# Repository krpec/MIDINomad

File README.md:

# MIDI Nomad

Arduino-based MIDI capable footswitch replacement for Mesa/Boogie Nomad 100 head.

Inspired by [happyswitch](https://happyswitch.it), [happyswitch github repo](https://github.com/siddolo/happyswitch)

Hackaday.io project can be found here: [MIDI Nomad](https://hackaday.io/project/170576-midi-nomad)

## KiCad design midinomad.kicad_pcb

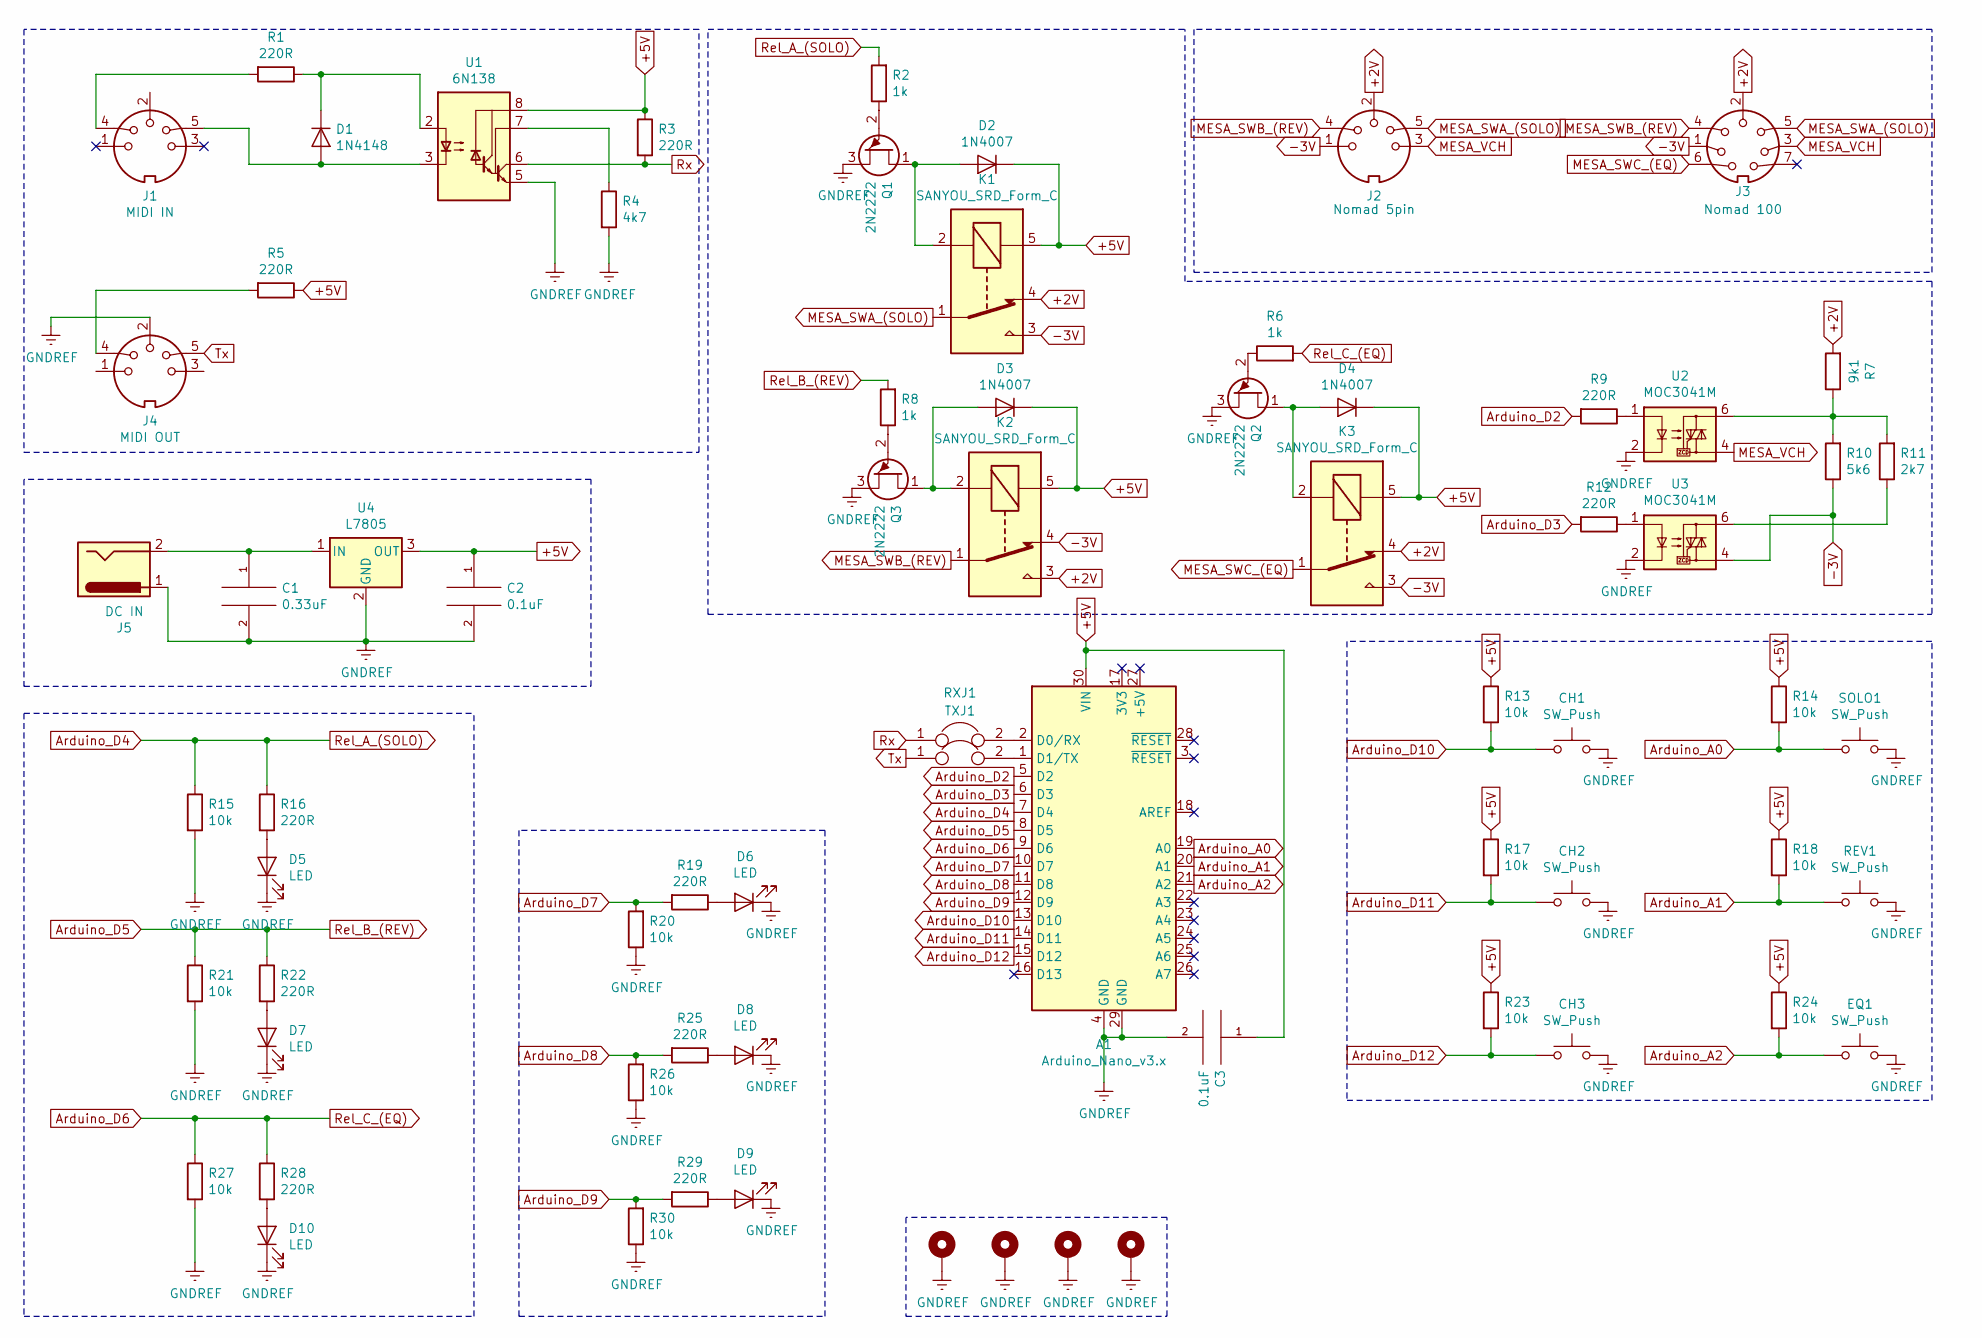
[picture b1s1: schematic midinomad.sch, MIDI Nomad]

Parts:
A1: Arduino_Nano_v3.x; Arduino_Nano
C1: 0.33uF; C_Disc_D6.0mm_W2.5mm_P5.00mm
C2, C3: 0.1uF; C_Disc_D6.0mm_W2.5mm_P5.00mm
CH1, CH2, CH3: SW_Push; SW_PUSH_6mm
D1: 1N4148; D_DO-35_SOD27_P7.62mm_Horizontal
D2, D3, D4: 1N4007; D_DO-41_SOD81_P10.16mm_Horizontal
D5, D6, D7, D8, D9, D10: LED; LED_D5.0mm
EQ1: SW_Push; SW_PUSH_6mm
H1, H2, H3, H4: MountingHole_Pad; MountingHole_3.2mm_M3_DIN965_Pad
J1: MIDI IN; din-5
J2: Nomad 5pin; din-5
J3: Nomad 100; din-8
J4: MIDI OUT; din-5
J5: DC IN; BarrelJack_Horizontal
K1, K2, K3: SANYOU_SRD_Form_C; Relay_SPDT_SANYOU_SRD_Series_Form_C
Q1, Q2, Q3: 2N2222; TO-92
R1, R3, R5, R9, R12, R16, R19, R22, R25, R28, R29: 220R; R_Axial_DIN0207_L6.3mm_D2.5mm_P10.16mm_Horizontal
R2, R6, R8: 1k; R_Axial_DIN0207_L6.3mm_D2.5mm_P10.16mm_Horizontal
R4: 4k7; R_Axial_DIN0207_L6.3mm_D2.5mm_P10.16mm_Horizontal
R7: 9k1; R_Axial_DIN0207_L6.3mm_D2.5mm_P10.16mm_Horizontal
R10: 5k6; R_Axial_DIN0207_L6.3mm_D2.5mm_P10.16mm_Horizontal
R11: 2k7; R_Axial_DIN0207_L6.3mm_D2.5mm_P10.16mm_Horizontal
R13, R14, R15, R17, R18, R20, R21, R23, R24, R26, R27, R30: 10k; R_Axial_DIN0207_L6.3mm_D2.5mm_P10.16mm_Horizontal
REV1: SW_Push; SW_PUSH_6mm
RXJ1: Jumper; PinHeader_1x02_P2.54mm_Vertical
SOLO1: SW_Push; SW_PUSH_6mm
TXJ1: Jumper; PinHeader_1x02_P2.54mm_Vertical
U1: 6N138; DIP-8_W7.62mm
U2, U3: MOC3041M; DIP-6_W7.62mm_LongPads
U4: L7805; TO-220-3_Vertical

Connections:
+2V: J2.2, J3.2, K1.4, K2.3, K3.4, R7.2
+5V: A1.30 (VIN), C2.1, C3.1, D2.1 (K), D3.1 (K), D4.1 (K), K1.5, K2.5, K3.5, R3.1, R5.1, R13.1, R14.1, R17.1, R18.1, R23.1, R24.1, U1.8 (VCC), U4.3 (OUT)
-3V: J2.1, J3.1, K1.3, K2.4, K3.3, R10.1, U3.4
Arduino_A0: A1.19 (A0), R14.2, SOLO1.1
Arduino_A1: A1.20 (A1), R18.2, REV1.1
Arduino_A2: A1.21 (A2), EQ1.1, R24.2
Arduino_D2: A1.5 (D2), R9.2
Arduino_D3: A1.6 (D3), R12.2
Arduino_D4: A1.7 (D4), R2.2, R15.1, R16.1
Arduino_D5: A1.8 (D5), R8.2, R21.1, R22.1
Arduino_D6: A1.9 (D6), R6.2, R27.1, R28.1
Arduino_D7: A1.10 (D7), R19.2, R20.2
Arduino_D8: A1.11 (D8), R25.2, R26.2
Arduino_D9: A1.12 (D9), R29.2, R30.2
Arduino_D10: A1.13 (D10), CH1.1, R13.2
Arduino_D11: A1.14 (D11), CH2.1, R17.2
Arduino_D12: A1.15 (D12), CH3.1, R23.2
GNDREF: A1.4 (GND), A1.29 (GND), C1.2, C2.2, C3.2, CH1.2, CH2.2, CH3.2, D5.1 (K), D6.1 (K), D7.1 (K), D8.1 (K), D9.1 (K), D10.1 (K), EQ1.2, H1.1, H2.1, H3.1, H4.1, J4.2, J5.1, Q1.3 (B1), Q2.3 (B1), Q3.3 (B1), R4.2, R15.2, R20.1, R21.2, R26.1, R27.2, R30.1, REV1.2, SOLO1.2, U1.5 (GND), U2.2, U3.2, U4.2 (GND)
MESA_SWA_(SOLO): J2.5, J3.5, K1.1
MESA_SWB_(REV): J2.4, J3.4, K2.1
MESA_SWC_(EQ): J3.6, K3.1
MESA_VCH: J2.3, J3.3, U2.4
unnamed: A1.1 (D1/TX), TXJ1.2
unnamed: A1.2 (D0/RX), RXJ1.2
unnamed: C1.1, J5.2, U4.1 (IN)
unnamed: D1.1 (K), R1.1, U1.2 (C1)
unnamed: D1.2 (A), J1.5, U1.3 (C2)
unnamed: D2.2 (A), K1.2, Q1.1 (B2)
unnamed: D3.2 (A), K2.2, Q3.1 (B2)
unnamed: D4.2 (A), K3.2, Q2.1 (B2)
unnamed: D5.2 (A), R16.2
unnamed: D6.2 (A), R19.1
unnamed: D7.2 (A), R22.2
unnamed: D8.2 (A), R25.1
unnamed: D9.2 (A), R29.1
unnamed: D10.2 (A), R28.2
unnamed: J1.4, R1.2
unnamed: J4.4, R5.2
unnamed: Q1.2 (E), R2.1
unnamed: Q2.2 (E), R6.1
unnamed: Q3.2 (E), R8.1
unnamed: R4.1, U1.7 (VO1)
unnamed: R9.1, U2.1
unnamed: R7.1, R10.2, R11.2, U2.6
unnamed: R11.1, U3.6
unnamed: R12.1, U3.1
Rx: R3.2, RXJ1.1, U1.6 (VO2)
Tx: J4.5, TXJ1.1

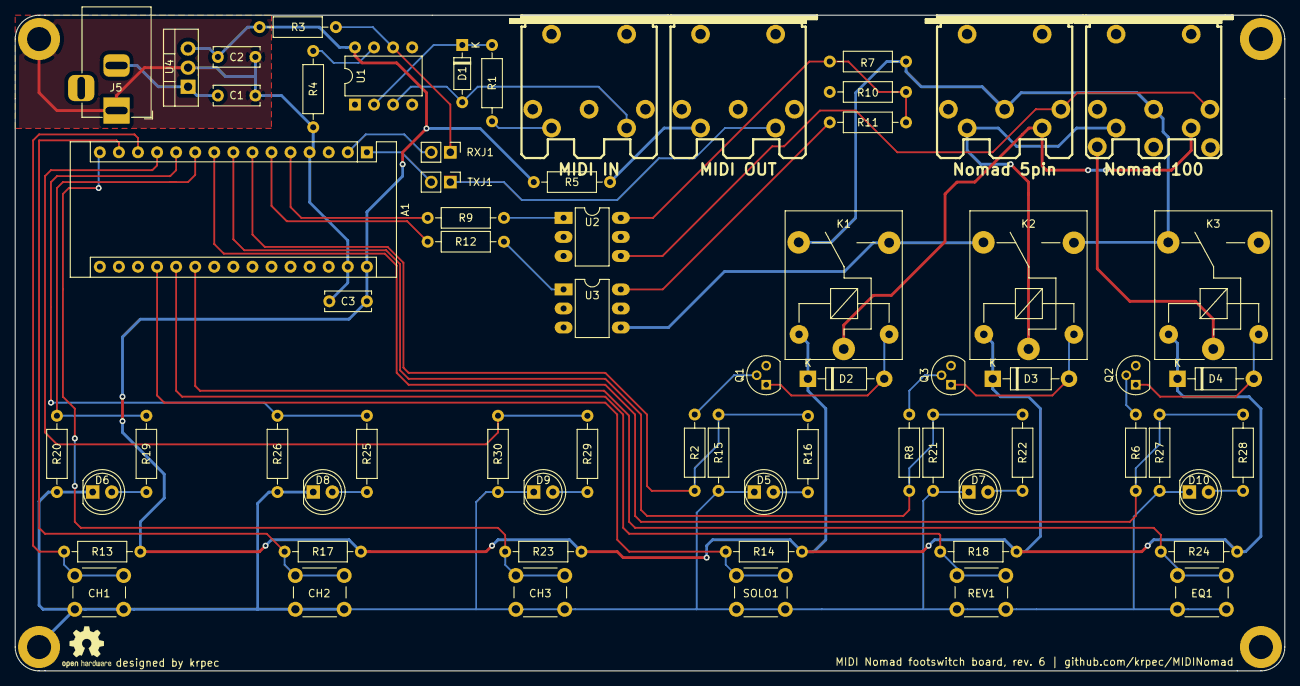
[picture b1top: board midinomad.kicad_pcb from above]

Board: 2 copper layers, 169.1 x 87.3 mm, 71 parts (0 on the bottom side), 48 nets.

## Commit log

2020-03-27 Initial schematics, no PCB yet.
2020-03-30 Updated schematics. Still work in progress.
2020-03-31 Schematics update, arduino code finished.
2020-04-01 schematics related changes
2020-04-04 schematics updated, using analog mux for vch switching, PCB nearly done
2020-04-05 Rev 4 schematics, rev 3 pcb
2020-04-05 forgot to f*$%ing save the changes..
2020-04-05 PCB rev. 4
2020-04-07 PCB changes
2020-04-07 Updated both schematics & PCB, added second 74hc4053.
2020-04-07 Updating internal program identification.
2020-04-07 Sketch changes
2020-04-07 MESA_SW values FIX
2020-04-07 Removed unnecessary code
2020-04-11 schematics changes
2020-04-13 Rev. 6 PCB & schematics
2021-01-05 before adding the rest of relays
